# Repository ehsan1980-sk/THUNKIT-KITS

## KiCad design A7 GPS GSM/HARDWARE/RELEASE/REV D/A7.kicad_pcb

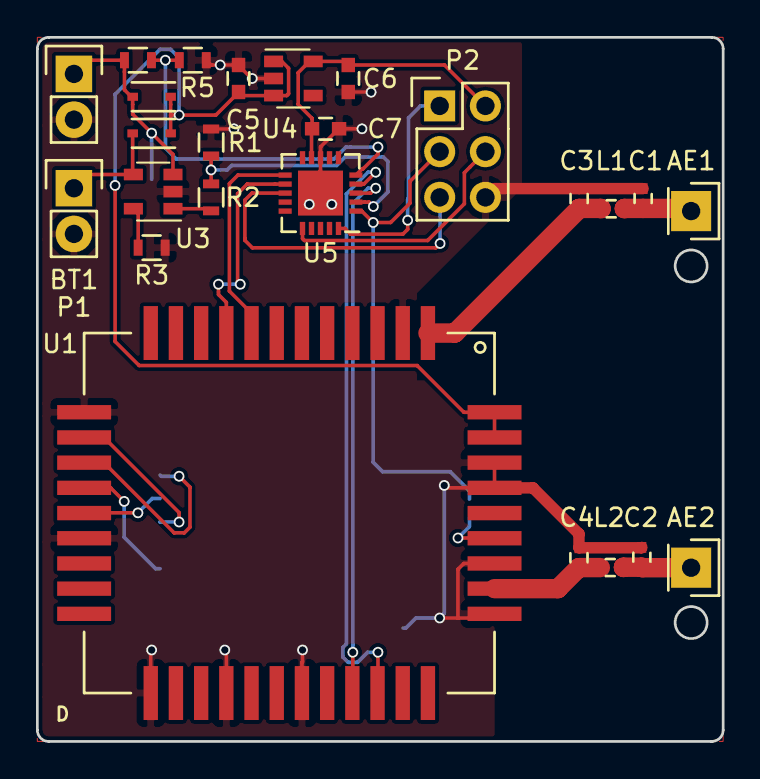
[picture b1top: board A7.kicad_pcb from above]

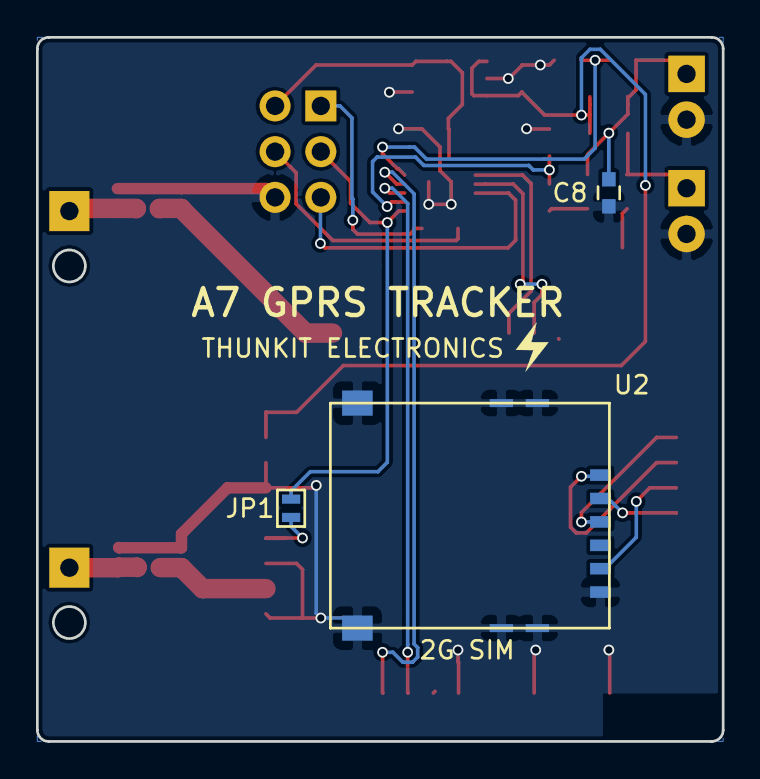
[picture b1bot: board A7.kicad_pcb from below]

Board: 2 copper layers, 38.1 x 39.1 mm, 28 parts (3 on the bottom side), 26 nets.

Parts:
AE1, AE2: λ/4 Wire; Pin_Header_Straight_1x01
BT1: 1S; Pin_Header_Straight_1x02
C1, C2, C3, C4: C; C_0402
C5, C6, C7: 1uF; C_0603
C8: 4.7uF; C_0603
D1, D2: S; SOD-323
JP1: 0; SOLDER JUMPER
L1, L2: L; C_0402
P1: CONN_01X02; Pin_Header_Straight_1x02
P2: ICSP; Pin_Header_Straight_2x03
R1, R2, R4, R5: R; R_0603
R3: 2K; R_0603
U1: A7
U2: 0786463001
U3: MCP73831T; SOT-23-5
U4: MIC5504-2.8YM5; SOT-23-5
U5: ATTINY841-MU; QFN-20-1EP_4x4mm_Pitch0.5mm

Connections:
A7_PWR: U1.8, U5.11
A7_SLEEP: U1.9, U5.12
BT_VCC: R4.1, R5.2, U5.5
CHRG_STAT: R1.2, R2.1, U5.2
GND: BT1.2, C1.2, C2.2, C3.2, C4.2, C5.2, C6.2, C7.2, C8.2, P1.2, P2.6, R1.1, R3.2, R5.1, U1.2, U1.13, U1.18, U1.22, U1.25, U1.28, U1.34, U1.36, U1.39, U1.40, U2.5, U3.2, U4.2, U5.8, U5.21
GPS_TX: JP1.1, U1.37
GSM_RX: U1.31, U5.4
GSM_TX: U1.30, U5.3
MISO: P2.1, U5.20
MOSI: P2.4, U5.16
unnamed: AE1.1, C1.1, L1.1
unnamed: AE2.1, C2.1, L2.1
unnamed: BT1.1, C8.1, D2.2, R4.2, U3.3
unnamed: C3.1, L1.2, U1.1
unnamed: C4.1, L2.2, U1.35
unnamed: D1.2, P1.1, U3.4
unnamed: R2.2, U3.1
unnamed: R3.1, U3.5
RST: P2.5, U5.13
SCK: JP1.2, P2.3, U5.1
SIM_CLK: U1.15, U2.3
SIM_IO: U1.17, U2.7
SIM_RST: U1.14, U2.2
SIM_VCC: U1.16, U2.1
VCC: C6.1, C7.1, P2.2, U4.5, U5.9
VIN: C5.1, D1.1, D2.1, U1.41, U1.42, U4.1, U4.3

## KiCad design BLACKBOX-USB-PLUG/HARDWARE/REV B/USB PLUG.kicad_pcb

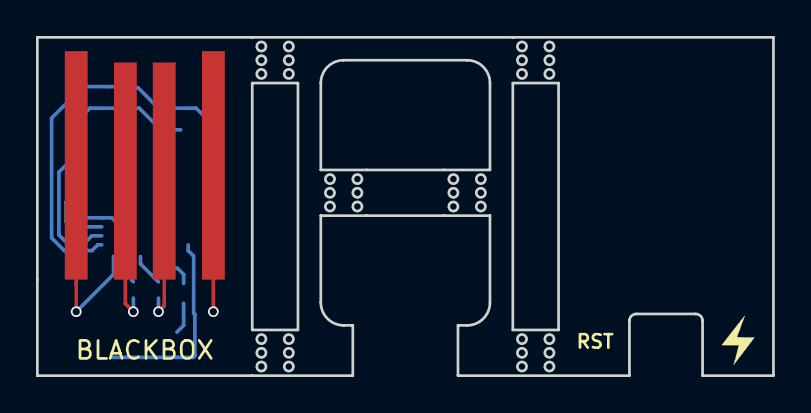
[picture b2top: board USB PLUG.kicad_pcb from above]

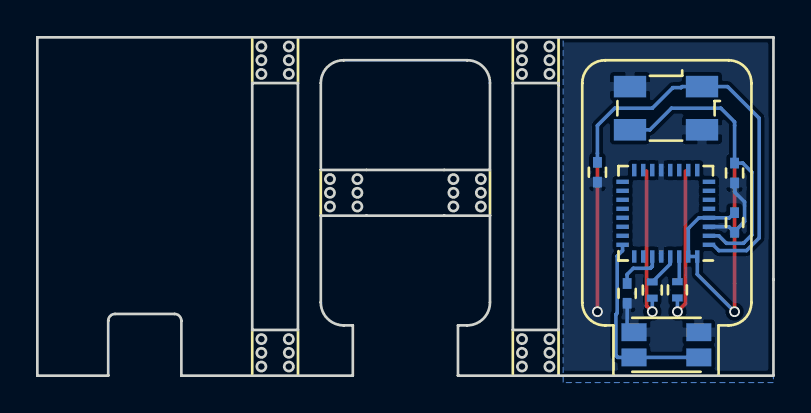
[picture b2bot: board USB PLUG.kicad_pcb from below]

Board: 2 copper layers, 40.9 x 18.8 mm, 10 parts (9 on the bottom side), 10 nets.

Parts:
C1, C2, C3, C4: C; C_0402
P1: USB_A; USB A PCB_modified
R1, R2: 22; R_0402
SW1: Push_SW; EVQ-P7A01P
U1: ATMEGA32U2; QFN-32-1EP_5x5mm_Pitch0.5mm
Y1: 16MHz; Crystal_SMD_ABM3B

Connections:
+5V: C4.2, P1.1, U1.4, U1.31, U1.32
GND: C1.2, C2.2, C3.1, C4.1, P1.4, SW1.2, U1.3, U1.13, U1.28, Y1.3
unnamed: C1.1, U1.1, Y1.1
unnamed: C2.1, U1.2, Y1.2
unnamed: C3.2, U1.27
unnamed: P1.2, R2.2
unnamed: P1.3, R1.2
unnamed: R1.1, U1.29
unnamed: R2.1, U1.30
unnamed: SW1.1, U1.24

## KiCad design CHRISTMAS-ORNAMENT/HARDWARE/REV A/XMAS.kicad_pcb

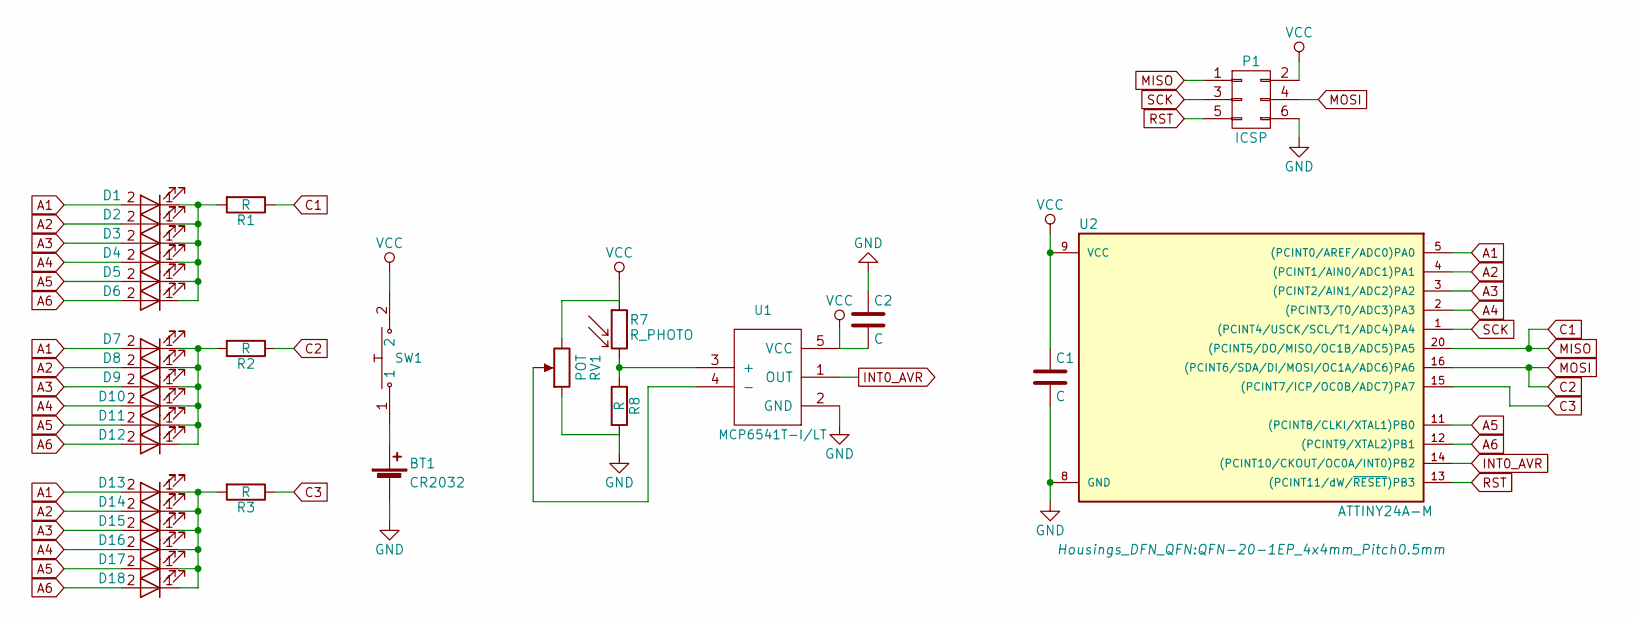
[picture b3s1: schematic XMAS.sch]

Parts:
BT1: CR2032; CR2032HARWIN
C1, C2: C; C_0603
D1, D2, D3, D4, D5, D6, D7, D8, D9, D10, D11, D12, D13, D14, D15, D16, D17, D18: LED; LED_0603
P1: ICSP; 2.54 ICSP
R1, R2, R3, R8: R; R_0603
R7: R_PHOTO; SMT_PHOTORESISTOR
RV1: POT; Potentiometer_Trimmer-EVM3E
SW1: Push_SW; JS102011JAQN_Handsoldering
U1: MCP6541T-I/LT; SOT-23-5
U2: ATTINY24A-M; QFN-20-1EP_4x4mm_Pitch0.5mm

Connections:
A1: D1.2 (A), D7.2 (A), D13.2 (A), U2.5 ((PCINT0/AREF/ADC0)PA0)
A2: D2.2 (A), D8.2 (A), D14.2 (A), U2.4 ((PCINT1/AIN0/ADC1)PA1)
A3: D3.2 (A), D9.2 (A), D15.2 (A), U2.3 ((PCINT2/AIN1/ADC2)PA2)
A4: D4.2 (A), D10.2 (A), D16.2 (A), U2.2 ((PCINT3/T0/ADC3)PA3)
A5: D5.2 (A), D11.2 (A), D17.2 (A), U2.11 ((PCINT8/CLKI/XTAL1)PB0)
A6: D6.2 (A), D12.2 (A), D18.2 (A), U2.12 ((PCINT9/XTAL2)PB1)
C1: P1.1, R1.1, U2.20 ((PCINT5/DO/MISO/OC1B/ADC5)PA5)
C2: P1.4, R2.1, U2.16 ((PCINT6/SDA/DI/MOSI/OC1A/ADC6)PA6)
C3: R3.1, U2.15 ((PCINT7/ICP/OC0B/ADC7)PA7)
GND: BT1.2 (-), C1.2, C2.1, P1.6, R8.2, RV1.1, U1.2 (GND), U2.8 (GND), U2.21
INT0_AVR: U1.1 (OUT), U2.14 ((PCINT10/CKOUT/OC0A/INT0)PB2)
unnamed: BT1.1 (+), SW1.1
unnamed: D1.1 (K), D2.1 (K), D3.1 (K), D4.1 (K), D5.1 (K), D6.1 (K), R1.2
unnamed: D7.1 (K), D8.1 (K), D9.1 (K), D10.1 (K), D11.1 (K), D12.1 (K), R2.2
unnamed: D13.1 (K), D14.1 (K), D15.1 (K), D16.1 (K), D17.1 (K), D18.1 (K), R3.2
unnamed: R7.2, R8.1, U1.3 (+)
unnamed: RV1.2, U1.4 (-)
RST: P1.5, U2.13 ((PCINT11/dW/~RESET~)PB3)
SCK: P1.3, U2.1 ((PCINT4/USCK/SCL/T1/ADC4)PA4)
VCC: C1.1, C2.2, P1.2, R7.1, RV1.3, SW1.2, U1.5 (VCC), U2.9 (VCC)

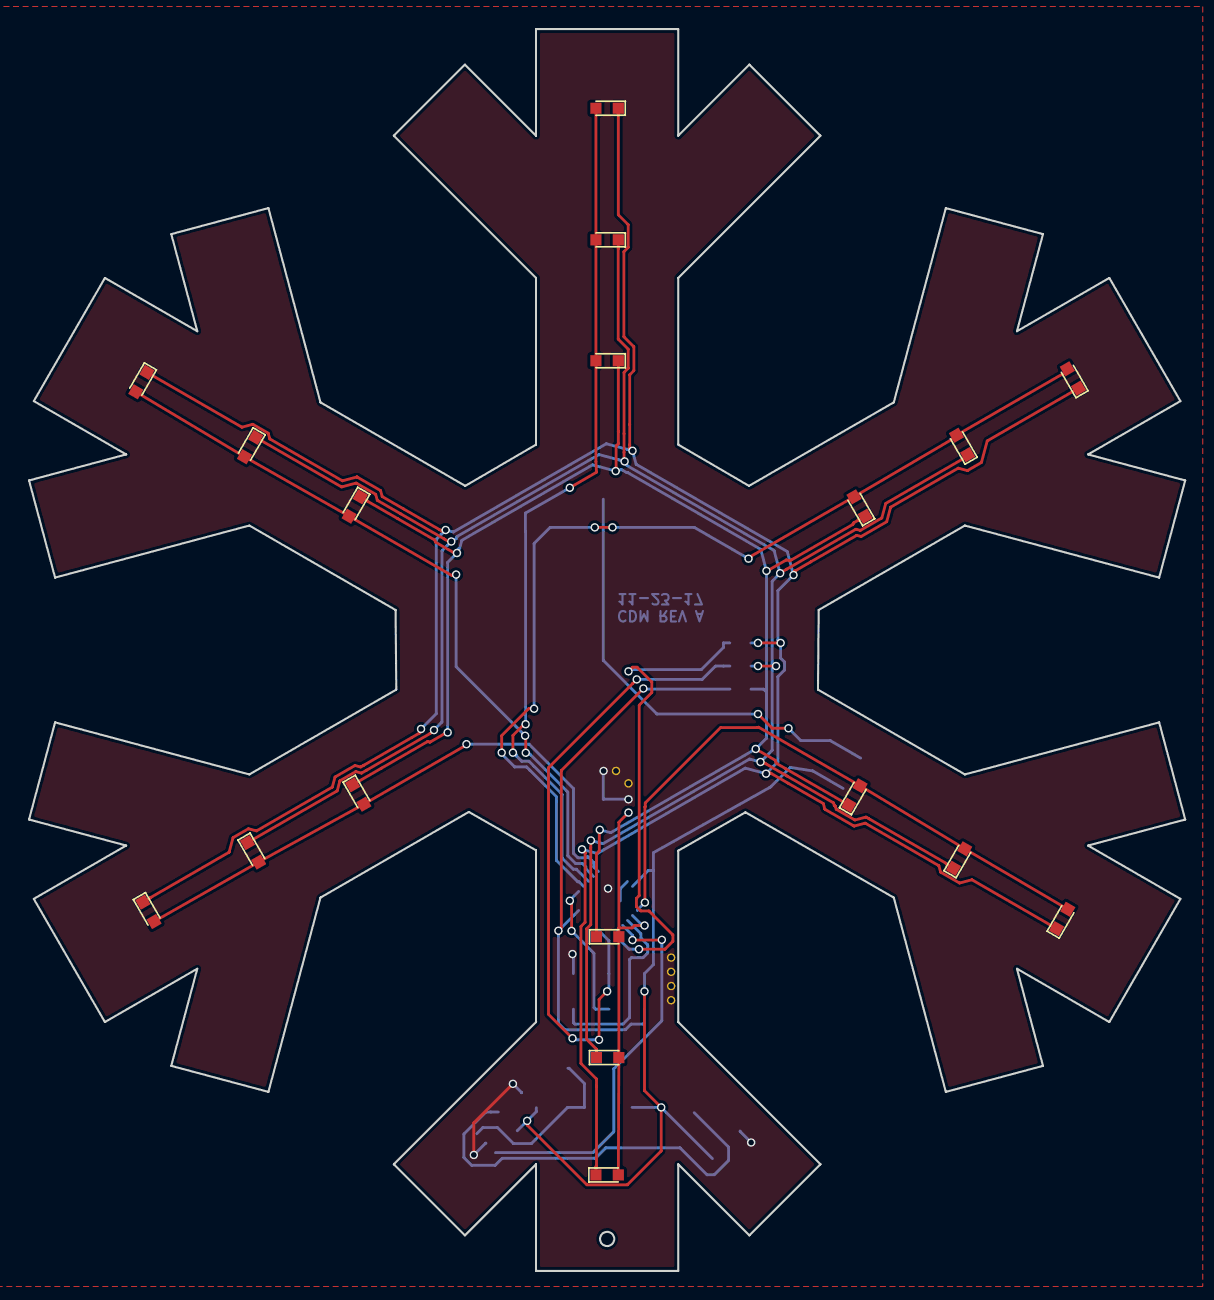
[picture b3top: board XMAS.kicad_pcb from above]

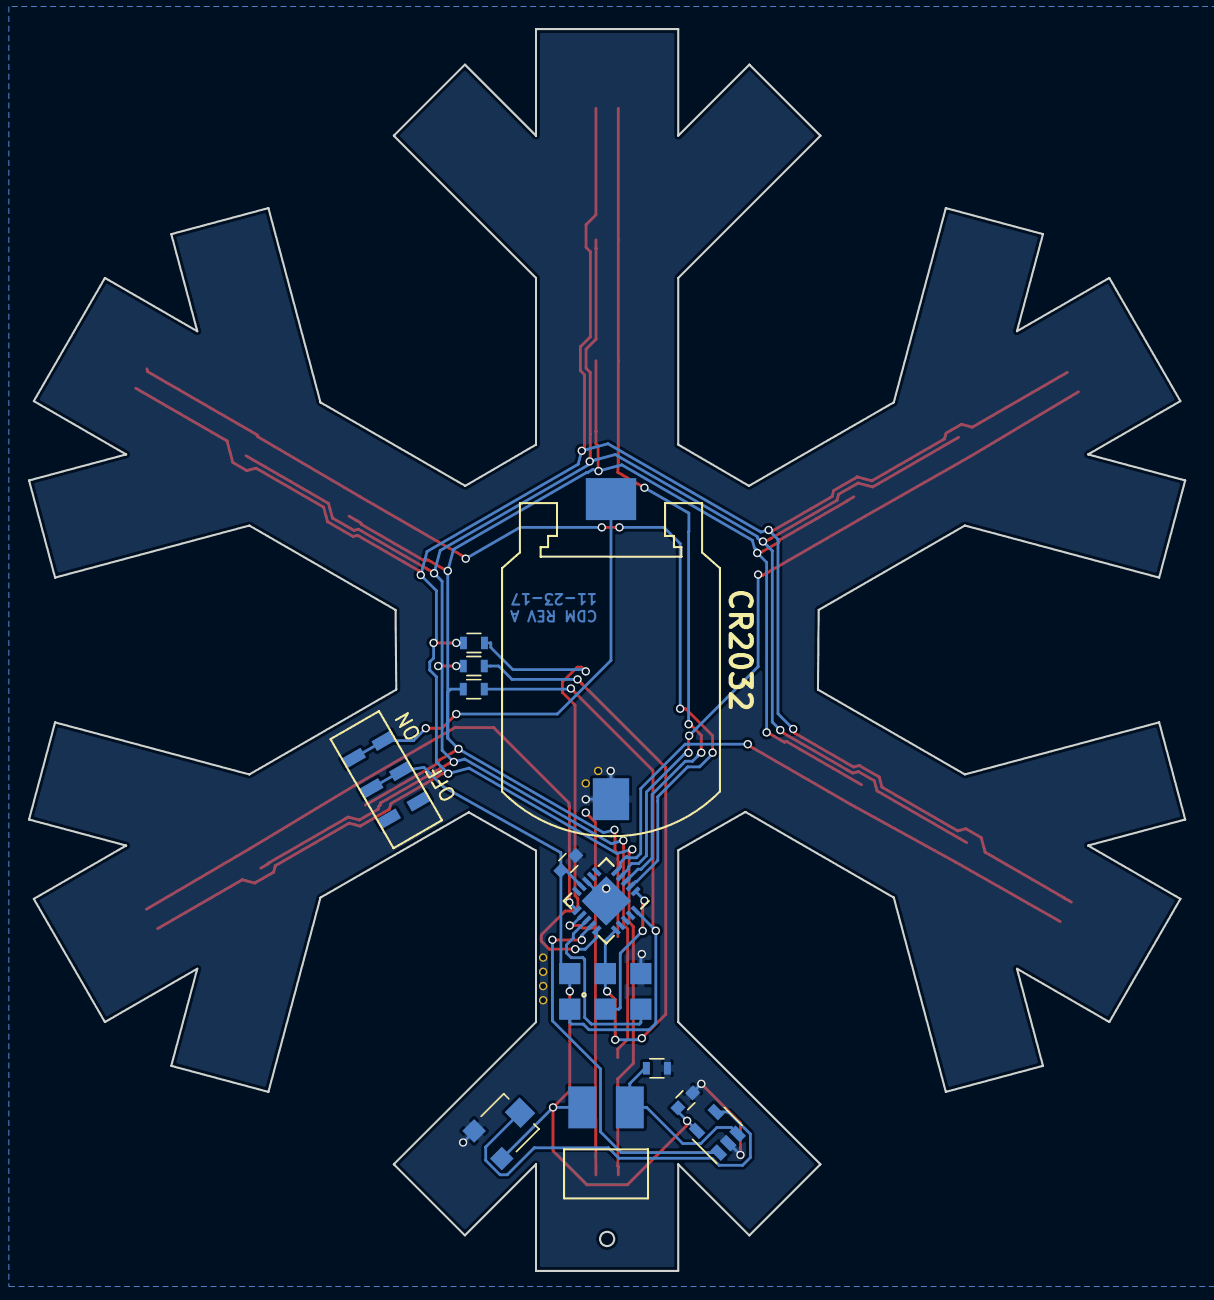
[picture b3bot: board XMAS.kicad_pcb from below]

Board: 2 copper layers, 82.6 x 88.7 mm, 31 parts (13 on the bottom side), 20 nets.

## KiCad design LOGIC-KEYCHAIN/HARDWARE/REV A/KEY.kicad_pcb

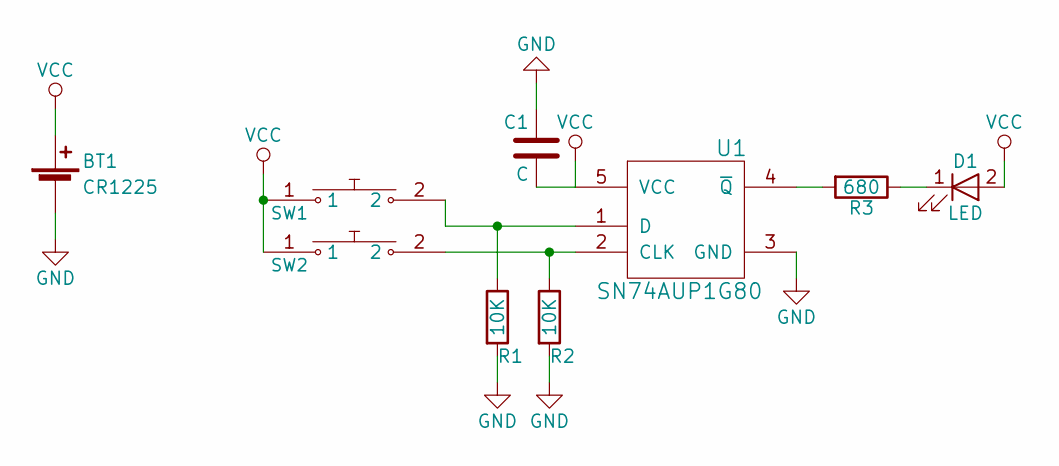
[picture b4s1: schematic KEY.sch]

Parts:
BT1: CR1225; BK-916
C1: C; C_0603
D1: LED; LED_0603
R1, R2: 10K; R_0603
R3: 680; R_0603
SW1, SW2: Push_SW; PTS810 SJK 250 SMTR LFS
U1: SN74AUP1G80; SOT-23-5

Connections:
GND: BT1.2 (-), C1.1, R1.2, R2.2, U1.3 (GND)
unnamed: D1.1 (K), R3.1
unnamed: R1.1, SW1.2, U1.1 (D)
unnamed: R2.1, SW2.2, U1.2 (CLK)
unnamed: R3.2, U1.4 (~Q)
VCC: BT1.1 (+), C1.2, D1.2 (A), SW1.1, SW2.1, U1.5 (VCC)

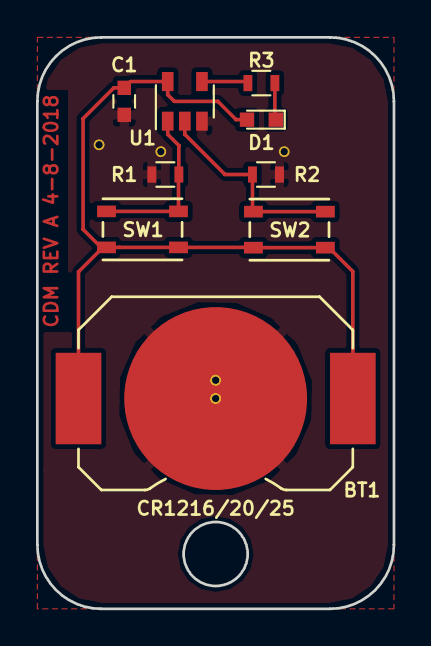
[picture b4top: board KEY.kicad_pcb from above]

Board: 2 copper layers, 19.8 x 31.8 mm, 9 parts (0 on the bottom side), 6 nets.

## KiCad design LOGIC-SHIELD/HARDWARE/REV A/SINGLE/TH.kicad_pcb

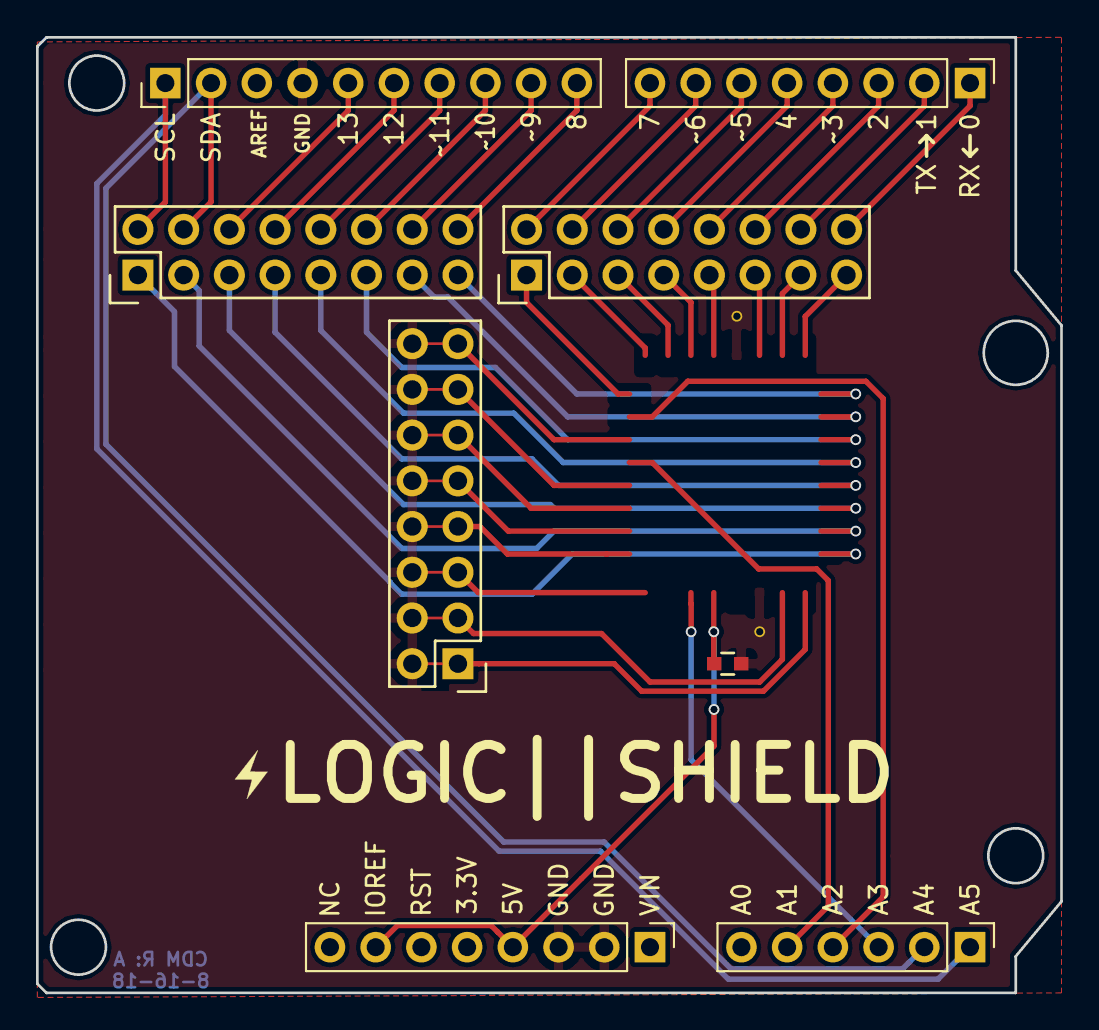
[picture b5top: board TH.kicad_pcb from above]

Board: 2 copper layers, 56.9 x 53.1 mm, 8 parts (0 on the bottom side), 18 nets.

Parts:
C1: 1uF; C_0603
P1, P2, P7: CONN_02X08; Pin_Header_Straight_2x08
P3, P6: CONN_01X08; Pin_Header_Straight_1x08_Pitch2.54mm
P4: CONN_01X06; Pin_Header_Straight_1x06_Pitch2.54mm
P5: CONN_01X10; Pin_Header_Straight_1x10_Pitch2.54mm

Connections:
+5V: C1.2, P3.4, P3.7
GND: C1.1, P2.2, P2.4, P2.6, P2.8, P2.10, P2.12, P2.14, P2.16, P3.2, P3.3, P5.4
PB0: P5.10, P7.16
PB1: P5.9, P7.14
PB2: P5.8, P7.12
PB3: P5.7, P7.10
PB4: P5.6, P7.8
PB5: P5.5, P7.6
PC4: P4.2, P5.2, P7.4
PC5: P4.1, P5.1, P7.2
PD0: P1.16, P6.1
PD1: P1.14, P6.2
PD2: P1.12, P6.3
PD3: P1.10, P6.4
PD4: P1.8, P6.5
PD5: P1.6, P6.6
PD6: P1.4, P6.7
PD7: P1.2, P6.8
